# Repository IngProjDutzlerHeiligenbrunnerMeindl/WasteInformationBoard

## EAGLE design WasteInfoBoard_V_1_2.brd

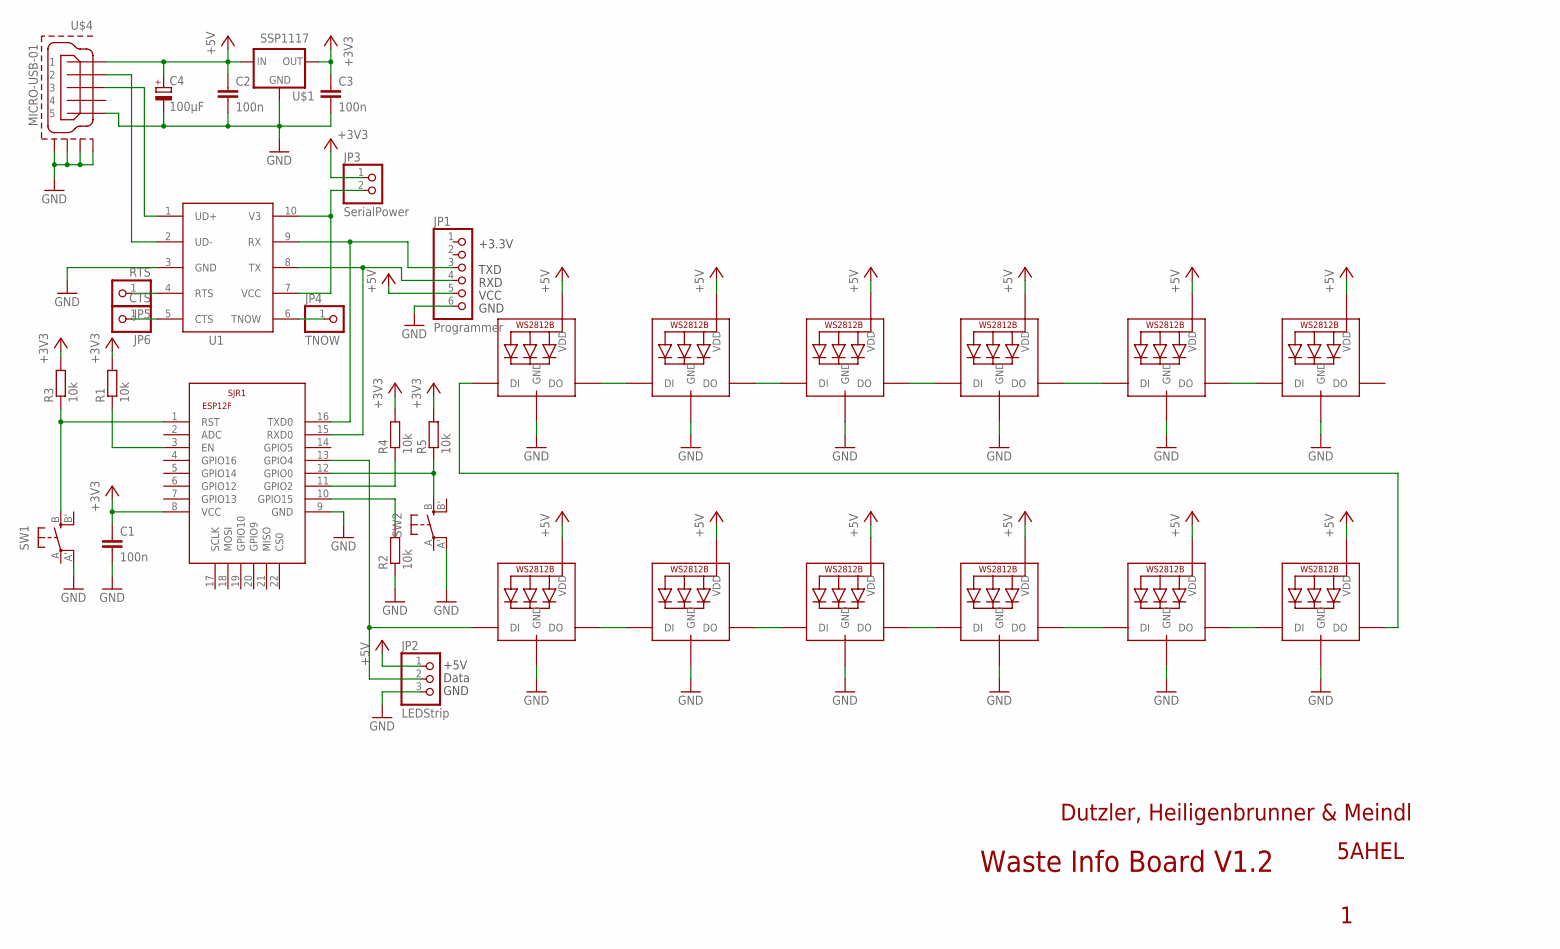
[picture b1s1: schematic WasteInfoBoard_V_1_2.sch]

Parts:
C1, C2, C3: 100n; C0805
C4: 100µF; 175TMP-0808
JP1: Programmer; 1X06
JP2: LEDStrip; 1X03
JP3: SerialPower; 1X02
JP4: TNOW; 1X01
JP5: RTS; 1X01
JP6: CTS; 1X01
LED1, LED2, LED3, LED4, LED5, LED6, LED7, LED8, LED9, LED10, LED11, LED12: WS2812B5050; WS2812B
R1, R2, R3, R4, R5: 10k; R0805
SJR1: ESP8266; ESP8266-ESP12E
SW1, SW2: SPST_TACT-EVQQ2; EVQ-Q2
U1: CH340ESMD; MSOP10
U$1: SSP1117; SOT223
U$4: MICRO-USB-01; 47589-0001

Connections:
+3V3: C1.1, C3.1, JP3.1, R1.2, R3.2, R4.2, R5.2, SJR1.8 (VCC), U$1.2 (OUT)
+5V: C2.1, C4.+, JP1.5, JP2.1, LED1.1-VDD (VDD), LED2.1-VDD (VDD), LED3.1-VDD (VDD), LED4.1-VDD (VDD), LED5.1-VDD (VDD), LED6.1-VDD (VDD), LED7.1-VDD (VDD), LED8.1-VDD (VDD), LED9.1-VDD (VDD), LED10.1-VDD (VDD), LED11.1-VDD (VDD), LED12.1-VDD (VDD), U$1.3 (IN), U$4.1
GND: C1.2, C2.2, C3.2, C4.-, JP1.6, JP2.3, LED1.3-GND (GND), LED2.3-GND (GND), LED3.3-GND (GND), LED4.3-GND (GND), LED5.3-GND (GND), LED6.3-GND (GND), LED7.3-GND (GND), LED8.3-GND (GND), LED9.3-GND (GND), LED10.3-GND (GND), LED11.3-GND (GND), LED12.3-GND (GND), R2.1, SJR1.9 (GND), SW1.A' (P1), SW2.A' (P1), U1.3 (GND), U$1.1 (GND), U$4.5, U$4.CASING1 (GND1), U$4.CASING2 (GND2), U$4.CASING3 (GND3), U$4.CASING4 (GND4)
unnamed: JP2.2, LED1.4-DIN (DI), SJR1.13 (GPIO4)
unnamed: R2.2, SJR1.10 (GPIO15)
unnamed: R3.1, SJR1.1 (RST), SW1.B (S)
unnamed: R1.1, SJR1.3 (EN)
unnamed: R4.1, SJR1.11 (GPIO2)
unnamed: R5.1, SJR1.12 (GPIO0), SW2.B (S)
unnamed: JP1.3, SJR1.16 (TXD0), U1.9 (RX)
unnamed: JP1.4, SJR1.15 (RXD0), U1.8 (TX)
unnamed: LED1.2-DOUT (DO), LED2.4-DIN (DI)
unnamed: LED2.2-DOUT (DO), LED3.4-DIN (DI)
unnamed: LED3.2-DOUT (DO), LED4.4-DIN (DI)
unnamed: LED4.2-DOUT (DO), LED5.4-DIN (DI)
unnamed: LED5.2-DOUT (DO), LED6.4-DIN (DI)
unnamed: LED7.2-DOUT (DO), LED8.4-DIN (DI)
unnamed: LED8.2-DOUT (DO), LED9.4-DIN (DI)
unnamed: LED9.2-DOUT (DO), LED10.4-DIN (DI)
unnamed: LED10.2-DOUT (DO), LED11.4-DIN (DI)
unnamed: LED11.2-DOUT (DO), LED12.4-DIN (DI)
unnamed: LED6.2-DOUT (DO), LED7.4-DIN (DI)
unnamed: U1.1 (UD+), U$4.3
unnamed: U1.2 (UD-), U$4.2
unnamed: JP3.2, U1.7 (VCC), U1.10 (V3)
unnamed: JP5.1, U1.4 (RTS)
unnamed: JP6.1, U1.5 (CTS)
unnamed: JP4.1, U1.6 (TNOW)

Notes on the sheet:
GND
VCC
TXD
RXD
Data
+5V
Waste Info Board V1.2
Dutzler, Heiligenbrunner & Meindl
5AHEL
+3.3V

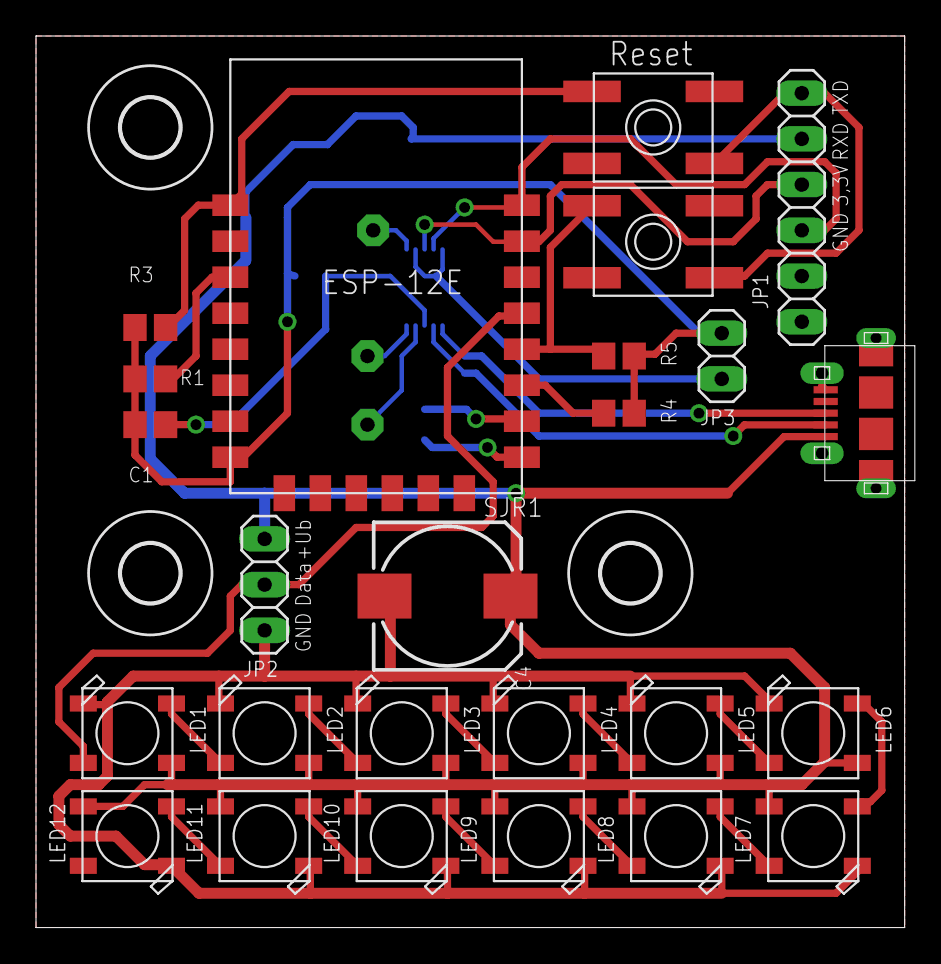
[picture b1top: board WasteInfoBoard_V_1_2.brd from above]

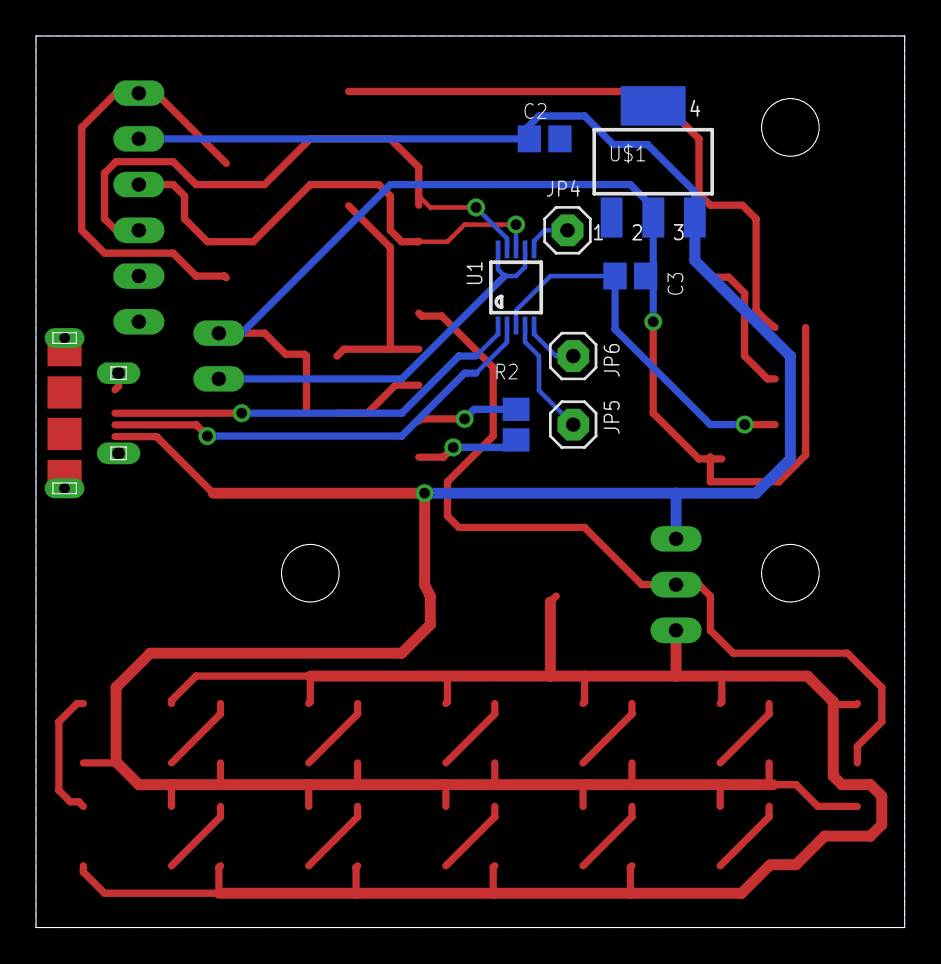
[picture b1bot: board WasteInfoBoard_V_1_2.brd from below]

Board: 2 copper layers, 48.3 x 49.5 mm, 36 parts (8 on the bottom side), 28 nets.

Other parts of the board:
U$2, U$3, U$5: 3,2

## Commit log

2020-04-30 Latest version of the WasteInformationBoard

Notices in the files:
parts and their libraries:
lm1117: (c) 2014 Samuel Lourenço
con-molex-usb: (C) 2014 Tomasz Boleslaw CEDRO, cederom@tlen.pl, http://www.tomek.cedro.info.
